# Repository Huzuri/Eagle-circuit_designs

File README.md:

# Eagle-circuit_designs
This are the circuit designed my Kaushik Huzuri using Camsoft Eagle software

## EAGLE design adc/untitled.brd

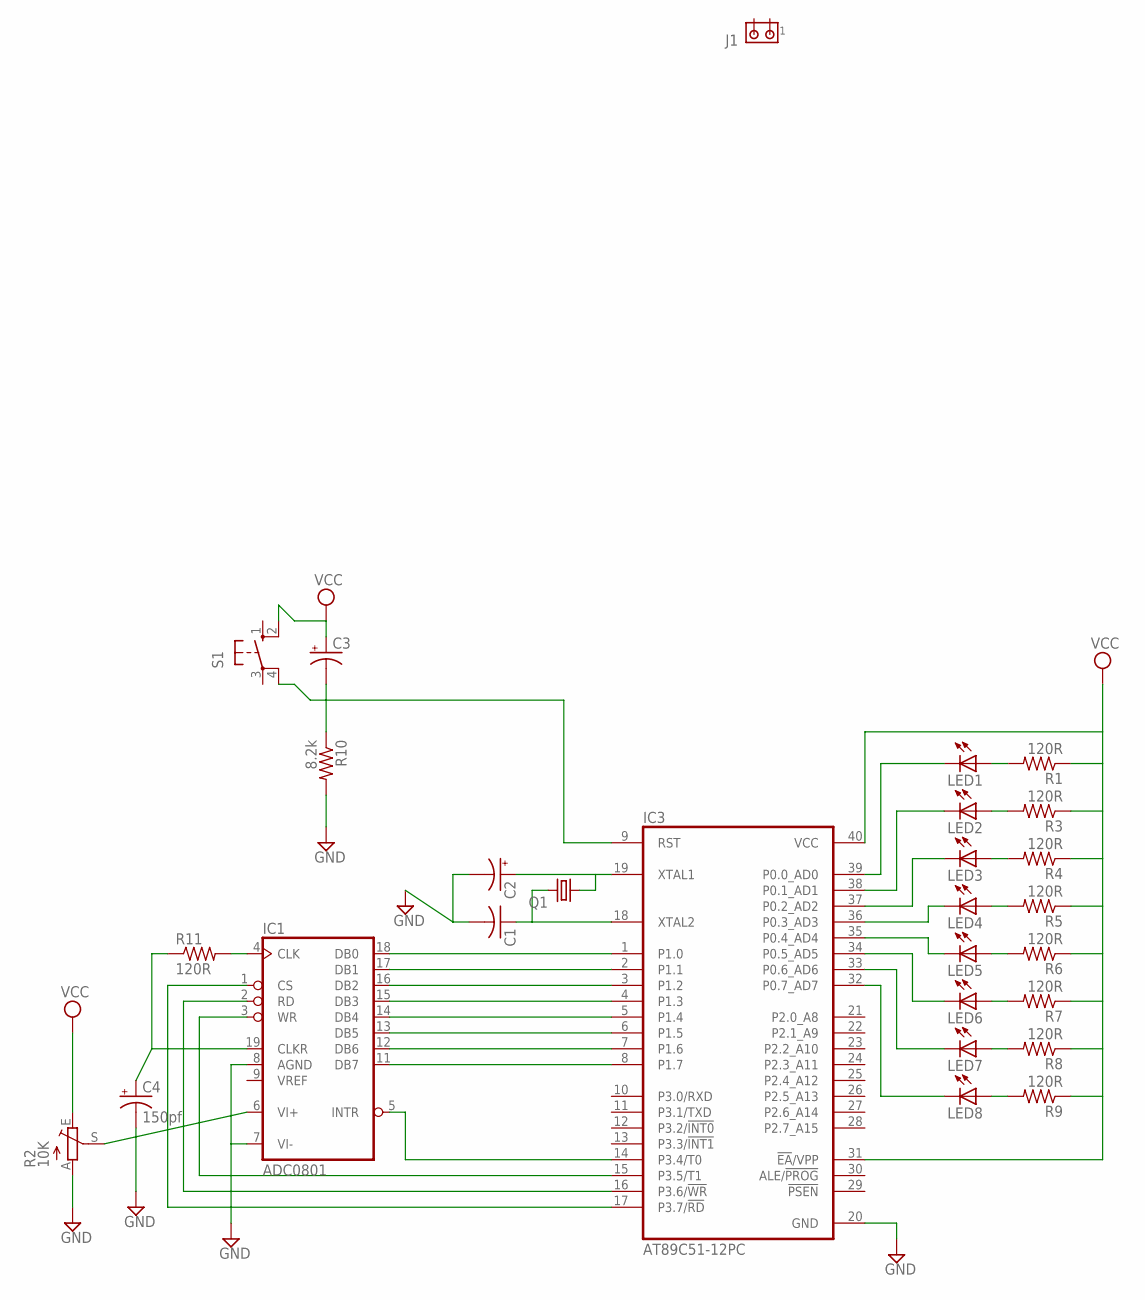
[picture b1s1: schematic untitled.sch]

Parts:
C1: C-US025-025X050; C025-025X050
C2, C3: CPOL-USE2.5-5V; E2,5-4R
C4: 150pf; E2,5-4R
IC1: ADC0801; DIL20
IC3: AT89C51-12PC; DIL40
J1: MTA02-100; 10X02MTA
LED1, LED2, LED3, LED4, LED5, LED6, LED7, LED8: LEDCHIP-LED0805; CHIP-LED0805
Q1: CRYSTALTC26H; TC26H
R1, R3, R4, R5, R6, R7, R8, R9, R11: 120R; R2512
R2: 10K; B25U
R10: 8.2k; R2512
S1: 10-XX; B3F-10XX

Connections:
GND: C1.2, C2.-, C4.-, IC1.7 (VI-), IC1.8 (AGND), IC1.10 (GND), IC3.20 (GND), R2.A, R10.2
unnamed: IC3.39 (P0.0_AD0), LED1.C
unnamed: IC3.32 (P0.7_AD7), LED8.C
unnamed: IC3.33 (P0.6_AD6), LED7.C
unnamed: IC3.38 (P0.1_AD1), LED2.C
unnamed: IC3.37 (P0.2_AD2), LED3.C
unnamed: IC3.34 (P0.5_AD5), LED6.C
unnamed: IC3.35 (P0.4_AD4), LED5.C
unnamed: IC3.36 (P0.3_AD3), LED4.C
unnamed: LED8.A, R9.2
unnamed: LED7.A, R8.2
unnamed: LED6.A, R7.2
unnamed: LED5.A, R6.2
unnamed: LED4.A, R5.2
unnamed: LED3.A, R4.2
unnamed: LED2.A, R3.2
unnamed: LED1.A, R1.2
unnamed: C2.+, IC3.19 (XTAL1), Q1.1
unnamed: C1.1, IC3.18 (XTAL2), Q1.2
unnamed: IC1.12 (DB6), IC3.7 (P1.6)
unnamed: C3.-, IC3.9 (RST), R10.1, S1.4 (P1)
unnamed: IC1.13 (DB5), IC3.6 (P1.5)
unnamed: IC1.14 (DB4), IC3.5 (P1.4)
unnamed: IC1.15 (DB3), IC3.4 (P1.3)
unnamed: IC1.16 (DB2), IC3.3 (P1.2)
unnamed: IC1.17 (DB1), IC3.2 (P1.1)
unnamed: IC1.11 (DB7), IC3.8 (P1.7)
unnamed: IC1.18 (DB0), IC3.1 (P1.0)
unnamed: IC1.5 (INTR), IC3.14 (P3.4/T0)
unnamed: IC1.3 (WR), IC3.15 (P3.5/T1)
unnamed: IC1.2 (RD), IC3.16 (P3.6/!WR)
unnamed: IC1.1 (CS), IC3.17 (P3.7/!RD)
unnamed: IC1.4 (CLK), R11.2
unnamed: C4.+, IC1.19 (CLKR), R11.1
unnamed: IC1.6 (VI+), R2.S
VCC: C3.+, IC1.20 (VCC), IC3.31 (!EA!/VPP), IC3.40 (VCC), R1.1, R2.E, R3.1, R4.1, R5.1, R6.1, R7.1, R8.1, R9.1, S1.2 (S1)

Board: 2 copper layers, 28 parts (0 on the bottom side), 36 nets, no tracks yet.

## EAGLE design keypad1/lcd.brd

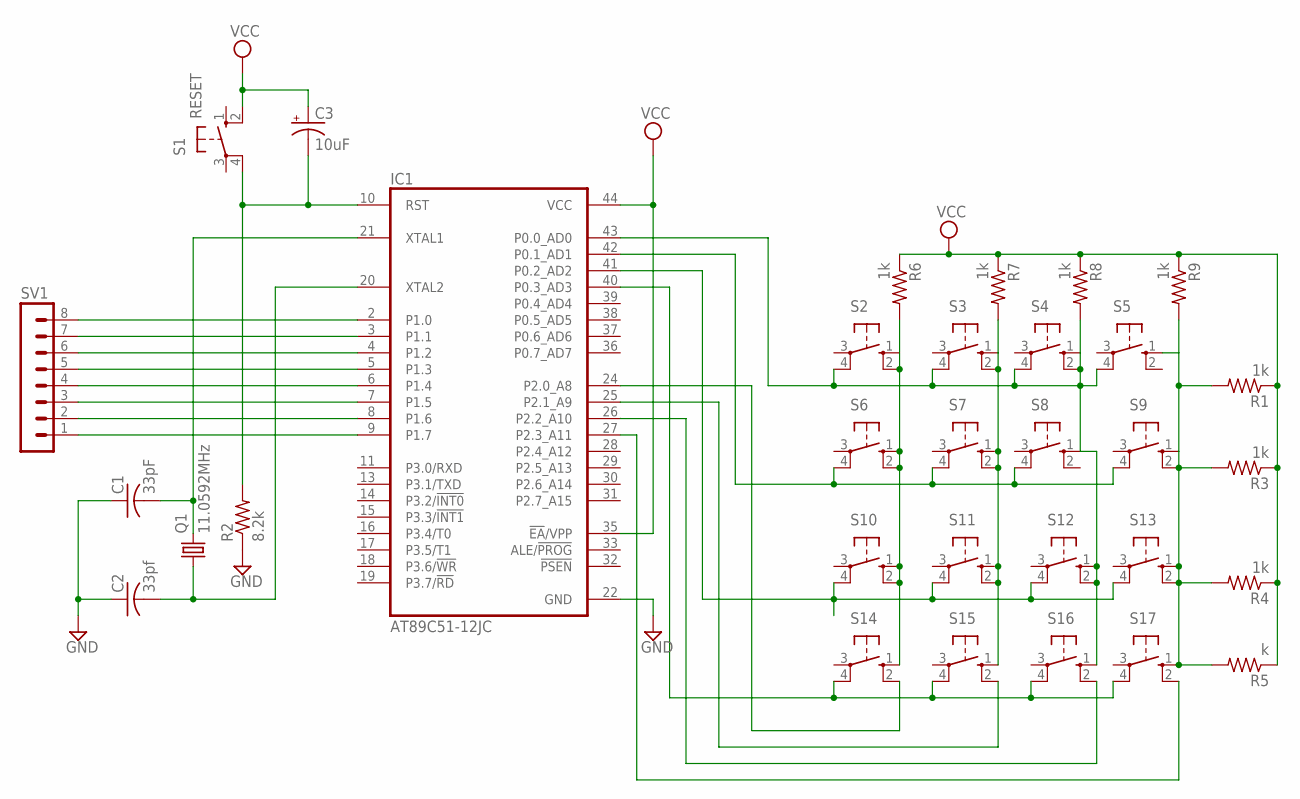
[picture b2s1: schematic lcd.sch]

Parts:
C1: 33pF; C025-025X050
C2: 33pf; C025-025X050
C3: 10uF; E2,5-5
IC1: AT89C51-12JC; PLCC44
Q1: 11.0592MHz; TC26H
R1, R3, R4, R6, R7, R8, R9: 1k; R2512
R2: 8.2k; R2512
R5: k; R2512
S1: RESET; B3F-10XX
S2, S3, S4, S5, S6, S7, S8, S9, S10, S11, S12, S13, S14, S15, S16, S17: 10-XX; B3F-10XX
SV1: MA08-1W

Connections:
GND: C1.1, C2.1, IC1.22 (GND), R2.1
unnamed: IC1.9 (P1.7), SV1.1
unnamed: IC1.8 (P1.6), SV1.2
unnamed: IC1.7 (P1.5), SV1.3
unnamed: IC1.6 (P1.4), SV1.4
unnamed: IC1.5 (P1.3), SV1.5
unnamed: IC1.4 (P1.2), SV1.6
unnamed: IC1.3 (P1.1), SV1.7
unnamed: IC1.2 (P1.0), SV1.8
unnamed: IC1.43 (P0.0_AD0), R8.2, S2.4 (P1), S3.4 (P1), S4.1 (S), S4.2 (S1), S4.4 (P1), S5.4 (P1), S8.1 (S), S12.1 (S), S12.2 (S1), S16.1 (S)
unnamed: IC1.42 (P0.1_AD1), S6.4 (P1), S7.4 (P1), S8.4 (P1), S9.4 (P1)
unnamed: IC1.41 (P0.2_AD2), S10.4 (P1), S11.4 (P1), S12.4 (P1), S13.4 (P1)
unnamed: C1.2, IC1.21 (XTAL1), Q1.2
unnamed: C2.2, IC1.20 (XTAL2), Q1.1
unnamed: IC1.40 (P0.3_AD3), S14.4 (P1), S15.4 (P1), S16.4 (P1), S17.4 (P1)
unnamed: IC1.25 (P2.1_A9), S15.2 (S1)
unnamed: C3.-, IC1.10 (RST), R2.2, S1.4 (P1)
unnamed: IC1.24 (P2.0_A8), S14.2 (S1)
unnamed: R6.2, S2.1 (S), S2.2 (S1), S6.1 (S), S6.2 (S1), S10.1 (S), S10.2 (S1), S14.1 (S)
unnamed: R7.2, S3.1 (S), S3.2 (S1), S7.1 (S), S7.2 (S1), S11.1 (S), S11.2 (S1), S15.1 (S)
unnamed: R1.2, R3.2, R4.2, R5.2, R9.2, S5.1 (S), S9.1 (S), S9.2 (S1), S13.1 (S), S13.2 (S1), S17.1 (S)
unnamed: IC1.26 (P2.2_A10), S16.2 (S1)
unnamed: IC1.27 (P2.3_A11), S17.2 (S1)
VCC: C3.+, IC1.35 (!EA!/VPP), IC1.44 (VCC), R1.1, R3.1, R4.1, R5.1, R6.1, R7.1, R8.1, R9.1, S1.2 (S1)

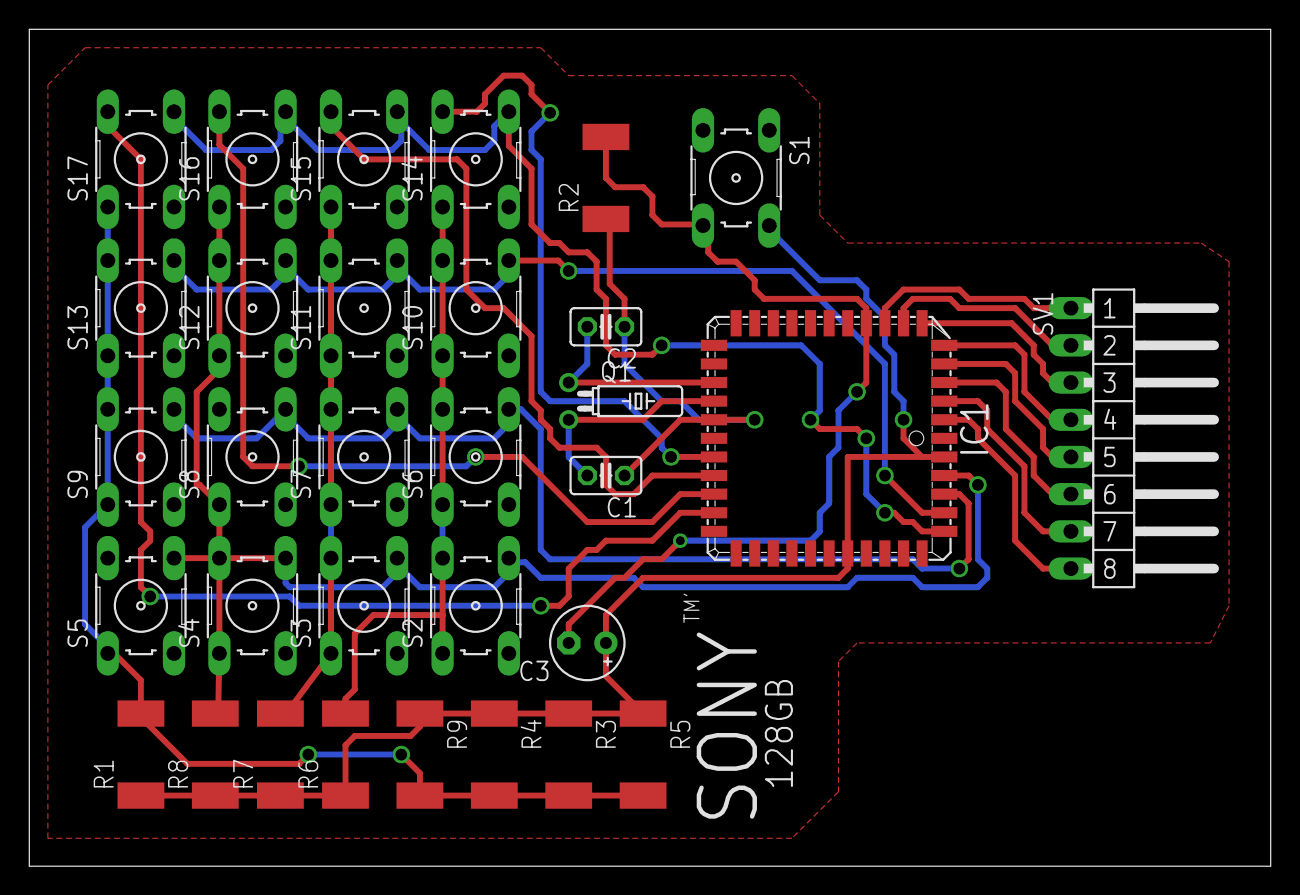
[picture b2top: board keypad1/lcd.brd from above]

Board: 2 copper layers, 84.8 x 57.1 mm, 32 parts (0 on the bottom side), 24 nets.

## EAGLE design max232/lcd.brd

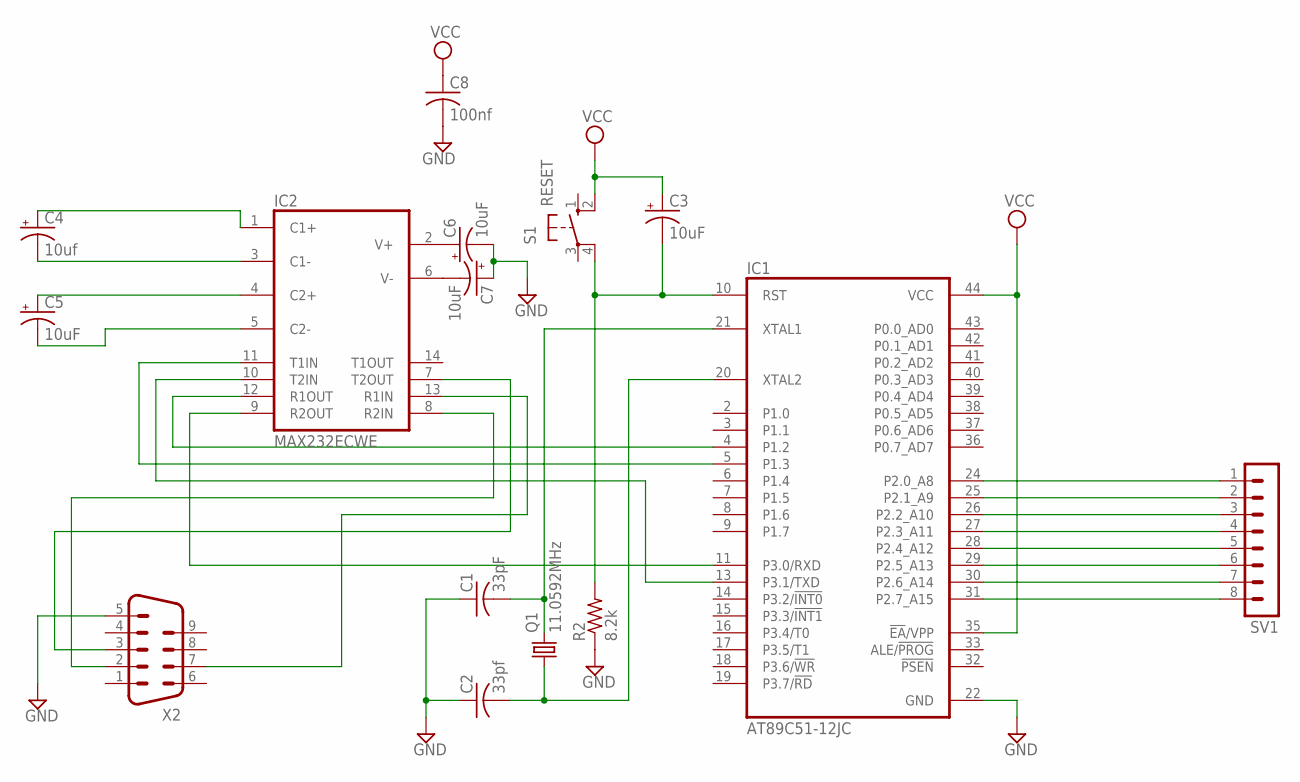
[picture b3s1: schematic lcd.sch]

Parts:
C1: 33pF; C025-025X050
C2: 33pf; C025-025X050
C3, C5, C6, C7: 10uF; E2,5-5
C4: 10uf; E2,5-5
C8: 100nf; C025-025X050
IC1: AT89C51-12JC; PLCC44
IC2: MAX232ECWE; SO16L
Q1: 11.0592MHz; TC26H
R2: 8.2k; R2512
S1: RESET; B3F-10XX
SV1: MA08-1W
X2: M09V

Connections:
GND: C1.1, C2.1, C6.-, C7.+, C8.2, IC1.22 (GND), IC2.15 (GND), R2.1, X2.5
unnamed: IC1.24 (P2.0_A8), SV1.1
unnamed: IC1.25 (P2.1_A9), SV1.2
unnamed: IC1.26 (P2.2_A10), SV1.3
unnamed: IC1.27 (P2.3_A11), SV1.4
unnamed: IC1.28 (P2.4_A12), SV1.5
unnamed: IC1.29 (P2.5_A13), SV1.6
unnamed: IC1.30 (P2.6_A14), SV1.7
unnamed: IC1.31 (P2.7_A15), SV1.8
unnamed: IC1.5 (P1.3), IC2.11 (T1IN)
unnamed: IC1.13 (P3.1/TXD), IC2.10 (T2IN)
unnamed: IC1.4 (P1.2), IC2.12 (R1OUT)
unnamed: C1.2, IC1.21 (XTAL1), Q1.2
unnamed: C2.2, IC1.20 (XTAL2), Q1.1
unnamed: IC1.11 (P3.0/RXD), IC2.9 (R2OUT)
unnamed: C4.+, IC2.1 (C1+)
unnamed: C4.-, IC2.3 (C1-)
unnamed: C3.-, IC1.10 (RST), R2.2, S1.4 (P1)
unnamed: C5.+, IC2.4 (C2+)
unnamed: C5.-, IC2.5 (C2-)
unnamed: C6.+, IC2.2 (V+)
unnamed: C7.-, IC2.6 (V-)
unnamed: IC2.7 (T2OUT), X2.3
unnamed: IC2.13 (R1IN), X2.7
unnamed: IC2.8 (R2IN), X2.2
VCC: C3.+, C8.1, IC1.35 (!EA!/VPP), IC1.44 (VCC), IC2.16 (VCC), S1.2 (S1)

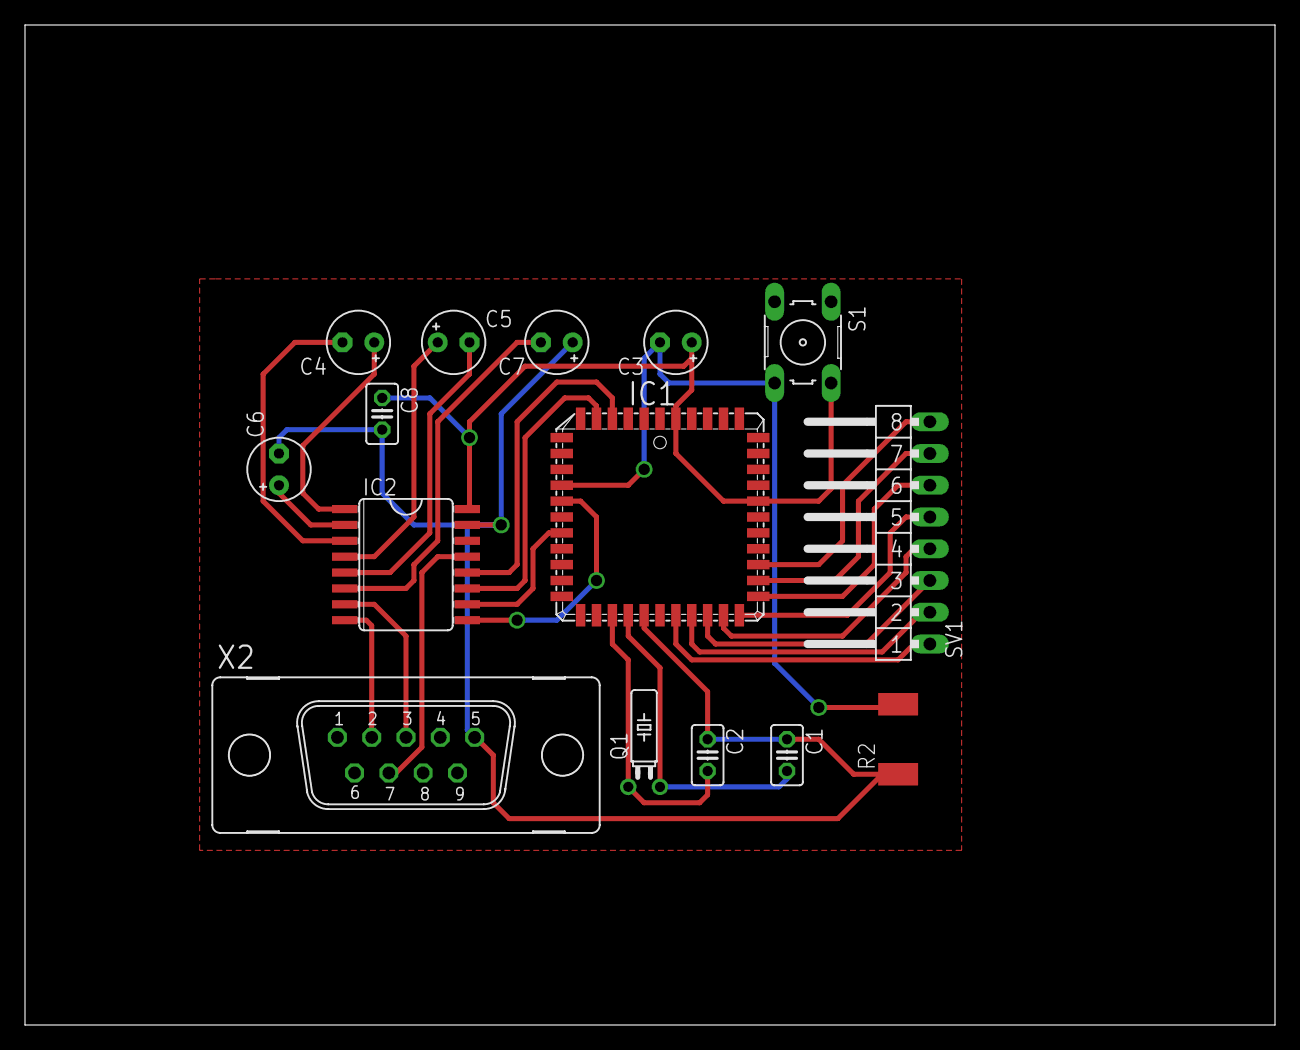
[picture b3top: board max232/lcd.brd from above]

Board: 2 copper layers, 100.0 x 80.0 mm, 15 parts (0 on the bottom side), 26 nets.

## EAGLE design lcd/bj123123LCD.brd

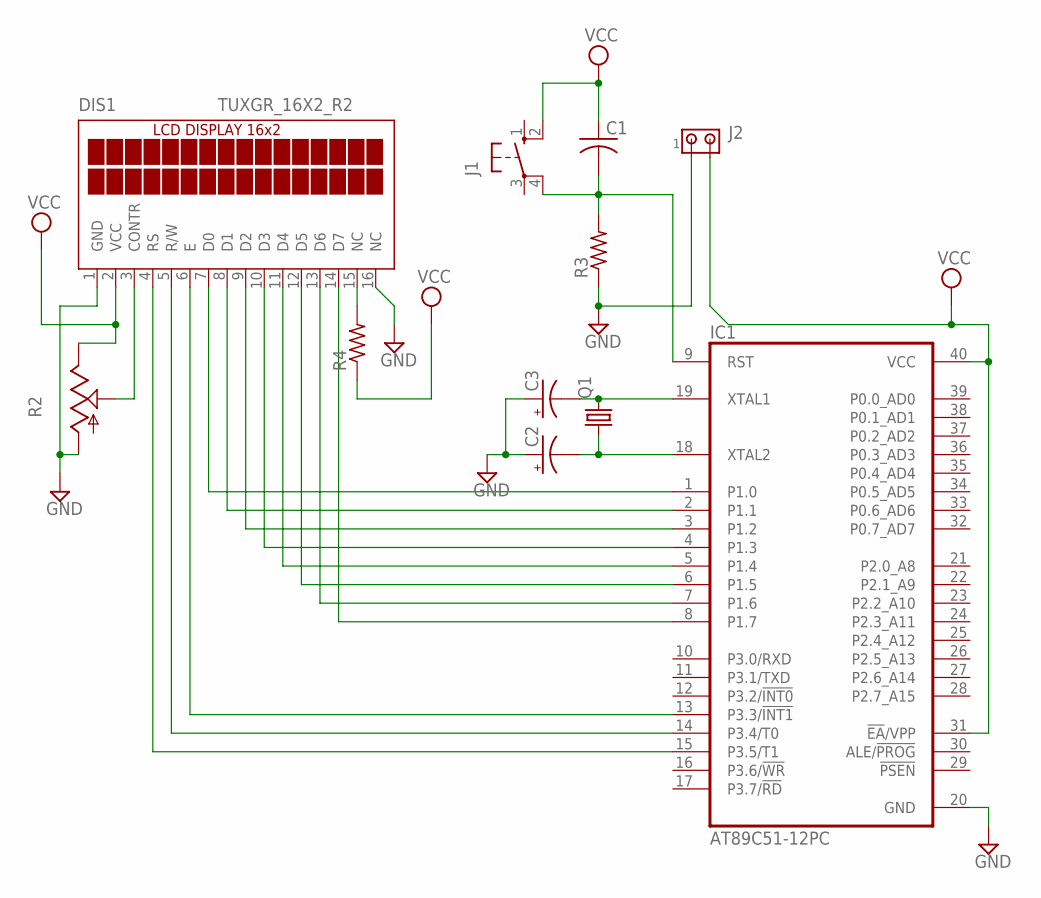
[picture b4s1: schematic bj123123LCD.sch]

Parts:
C1: C-US025-025X050; C025-025X050
C2, C3: CPOL-USE2.5-5; E2,5-5
DIS1: TUXGR_16X2_R2
IC1: AT89C51-12PC; DIL40
J1: 10-XX; B3F-10XX
J2: MTA02-100; 10X02MTA
Q1: CRYSTALTC26H; TC26H
R2: TRIM_US-B25U; B25U
R3, R4: R-US_R2512; R2512

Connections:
GND: C2.+, C3.+, DIS1.1 (GND), DIS1.16 (NC), IC1.20 (GND), J2.1, R2.A, R3.1
unnamed: DIS1.7 (D0), IC1.1 (P1.0)
unnamed: DIS1.8 (D1), IC1.2 (P1.1)
unnamed: DIS1.9 (D2), IC1.3 (P1.2)
unnamed: DIS1.10 (D3), IC1.4 (P1.3)
unnamed: DIS1.11 (D4), IC1.5 (P1.4)
unnamed: DIS1.12 (D5), IC1.6 (P1.5)
unnamed: DIS1.13 (D6), IC1.7 (P1.6)
unnamed: DIS1.14 (D7), IC1.8 (P1.7)
unnamed: DIS1.15 (NC), R4.2
unnamed: C3.-, IC1.19 (XTAL1), Q1.2
unnamed: C1.2, IC1.9 (RST), J1.4 (P1), R3.2
unnamed: C2.-, IC1.18 (XTAL2), Q1.1
unnamed: DIS1.6 (E), IC1.13 (P3.3/!INT1)
unnamed: DIS1.5 (R/W), IC1.14 (P3.4/T0)
unnamed: DIS1.3 (CONTR), R2.S
unnamed: DIS1.4 (RS), IC1.15 (P3.5/T1)
VCC: C1.1, DIS1.2 (VCC), IC1.31 (!EA!/VPP), IC1.40 (VCC), J1.2 (S1), J2.2, R2.E, R4.1

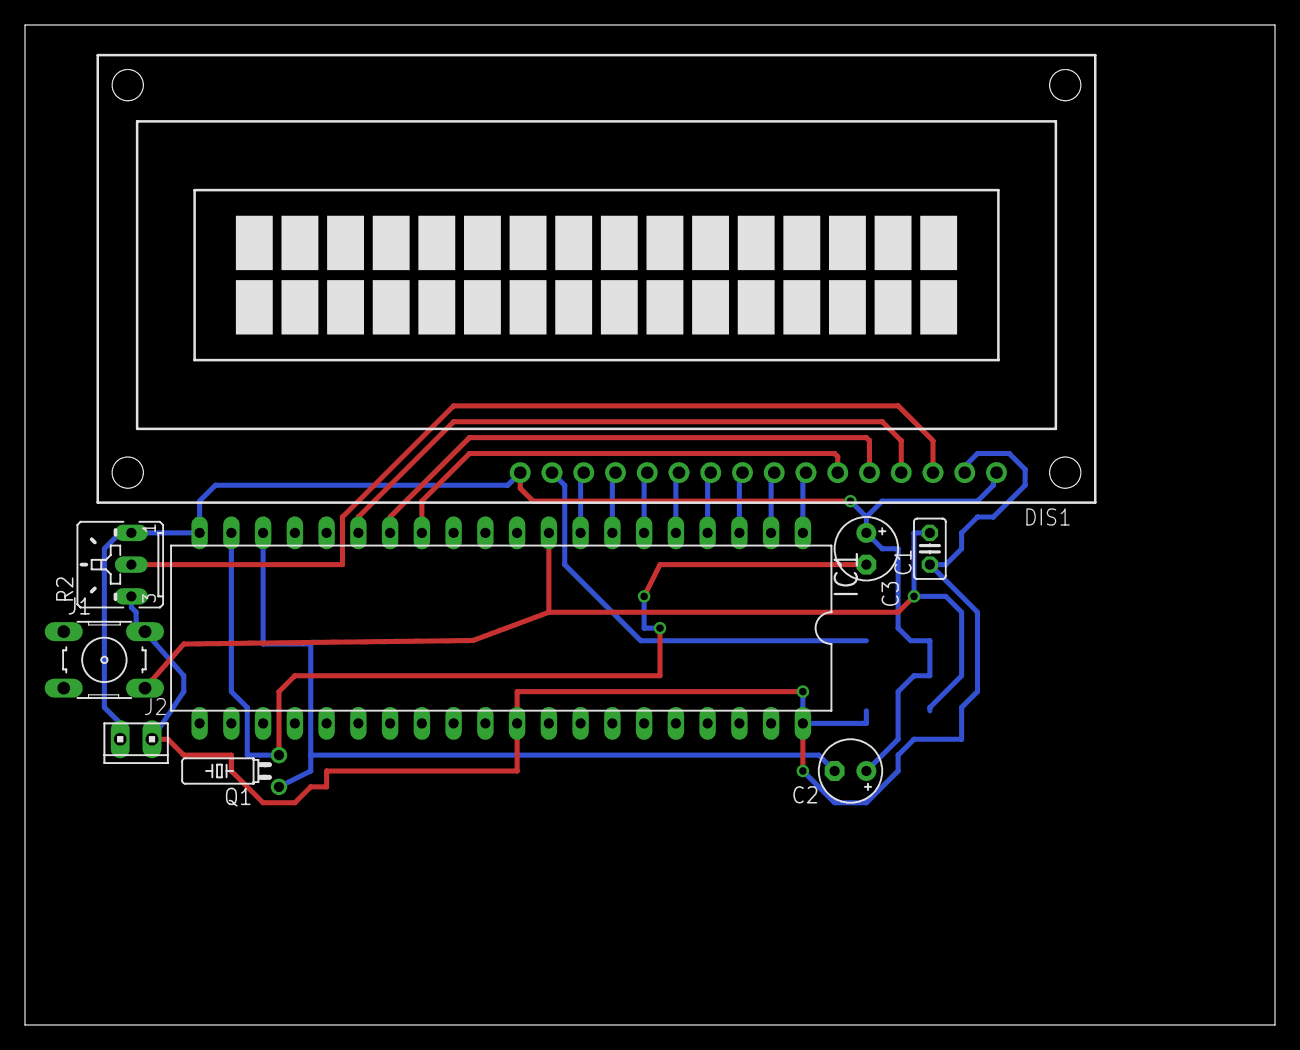
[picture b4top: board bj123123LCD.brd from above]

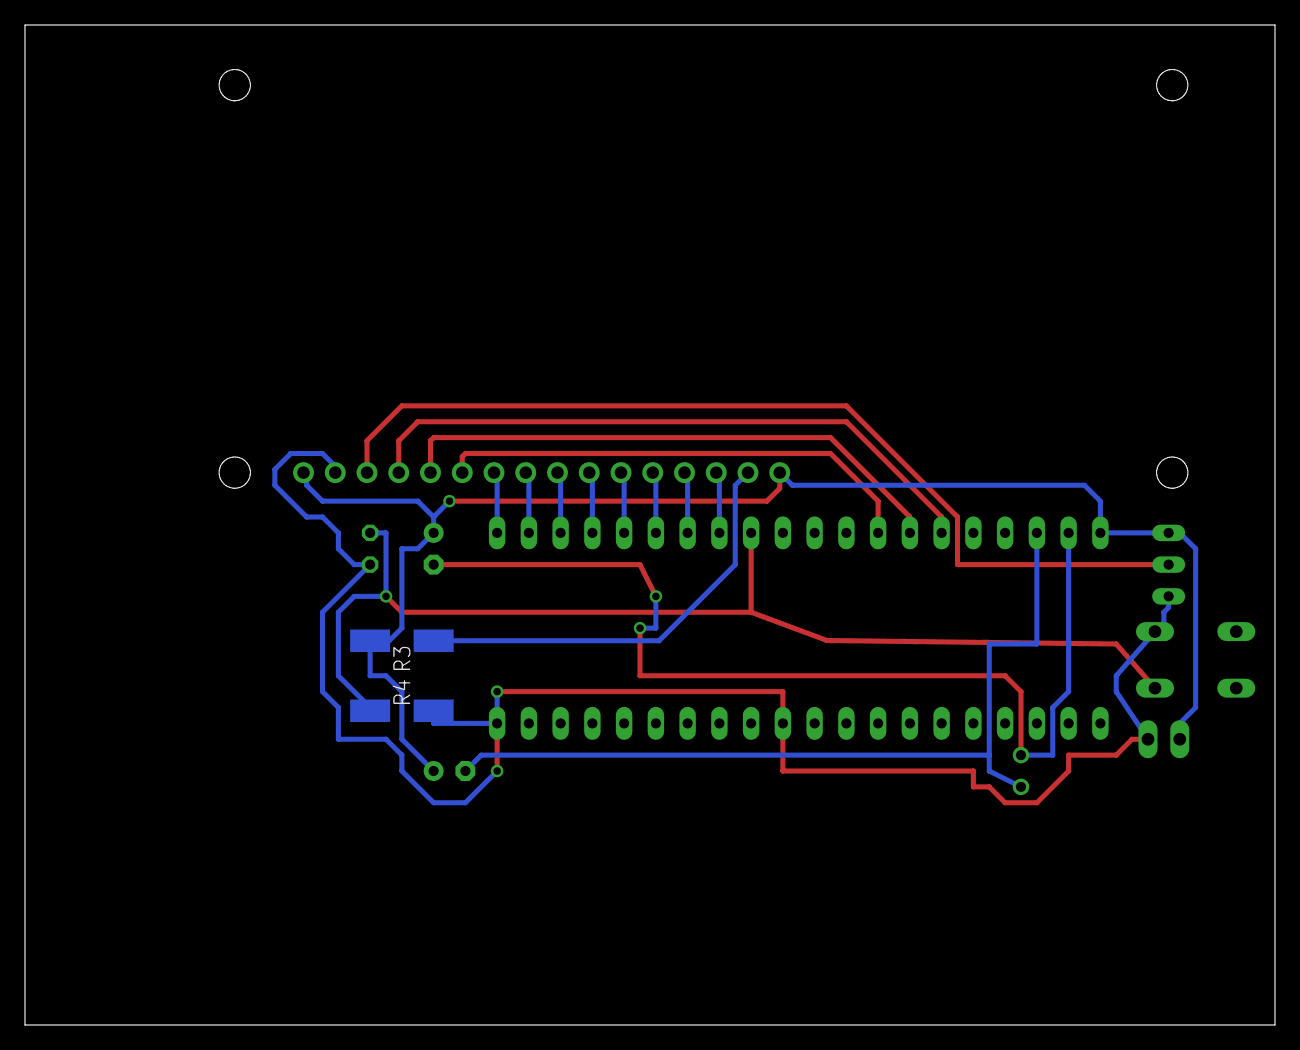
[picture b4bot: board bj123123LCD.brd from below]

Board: 2 copper layers, 100.0 x 80.0 mm, 11 parts (2 on the bottom side), 18 nets.

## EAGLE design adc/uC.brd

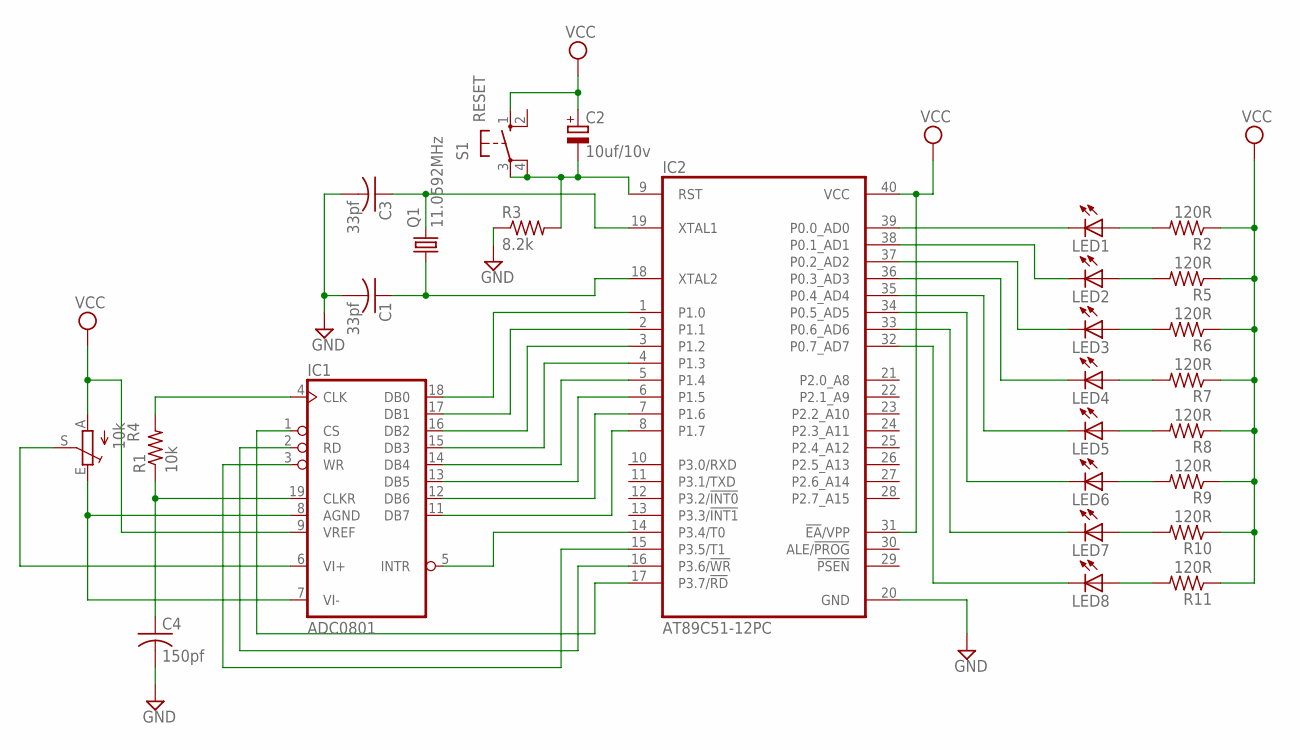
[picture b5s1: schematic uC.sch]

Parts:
C1, C3: 33pf; C025-025X050
C2: 10uf/10v; E2,5-5
C4: 150pf; C025-025X050
IC1: ADC0801; DIL20
IC2: AT89C51-12PC; DIL40
LED1, LED2, LED3, LED4, LED5, LED6, LED7, LED8: LEDCHIPLED_0805; CHIPLED_0805
Q1: 11.0592MHz; TC26H
R1: 10k; R2512
R2, R5, R6, R7, R8, R9, R10, R11: 120R; R2512
R3: 8.2k; R2512
R4: 10k; B25U
S1: RESET; B3F-10XX

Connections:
GND: C1.2, C3.2, C4.2, IC1.10 (GND), IC2.20 (GND), R3.1
unnamed: IC2.39 (P0.0_AD0), LED1.C
unnamed: IC2.38 (P0.1_AD1), LED2.C
unnamed: IC2.37 (P0.2_AD2), LED3.C
unnamed: IC2.36 (P0.3_AD3), LED4.C
unnamed: IC2.35 (P0.4_AD4), LED5.C
unnamed: IC2.34 (P0.5_AD5), LED6.C
unnamed: IC2.33 (P0.6_AD6), LED7.C
unnamed: IC2.32 (P0.7_AD7), LED8.C
unnamed: IC1.18 (DB0), IC2.1 (P1.0)
unnamed: IC1.17 (DB1), IC2.2 (P1.1)
unnamed: IC1.16 (DB2), IC2.3 (P1.2)
unnamed: IC1.15 (DB3), IC2.4 (P1.3)
unnamed: IC1.14 (DB4), IC2.5 (P1.4)
unnamed: IC1.13 (DB5), IC2.6 (P1.5)
unnamed: IC1.12 (DB6), IC2.7 (P1.6)
unnamed: IC1.11 (DB7), IC2.8 (P1.7)
unnamed: IC1.1 (CS), IC2.17 (P3.7/!RD)
unnamed: IC1.2 (RD), IC2.16 (P3.6/!WR)
unnamed: IC1.3 (WR), IC2.15 (P3.5/T1)
unnamed: IC1.5 (INTR), IC2.14 (P3.4/T0)
unnamed: IC1.6 (VI+), R4.S
unnamed: IC1.4 (CLK), R1.2
unnamed: IC1.7 (VI-), IC1.8 (AGND), R4.E
unnamed: C4.1, IC1.19 (CLKR), R1.1
unnamed: C2.-, IC2.9 (RST), R3.2, S1.3, S1.4 (P1)
unnamed: LED1.A, R2.2
unnamed: LED2.A, R5.2
unnamed: C3.1, IC2.19 (XTAL1), Q1.2
unnamed: C1.1, IC2.18 (XTAL2), Q1.1
unnamed: LED3.A, R6.2
unnamed: LED4.A, R7.2
unnamed: LED5.A, R8.2
unnamed: LED6.A, R9.2
unnamed: LED7.A, R10.2
unnamed: LED8.A, R11.2
VCC: C2.+, IC1.9 (VREF), IC1.20 (VCC), IC2.31 (!EA!/VPP), IC2.40 (VCC), R2.1, R4.A, R5.1, R6.1, R7.1, R8.1, R9.1, R10.1, R11.1, S1.1 (S)

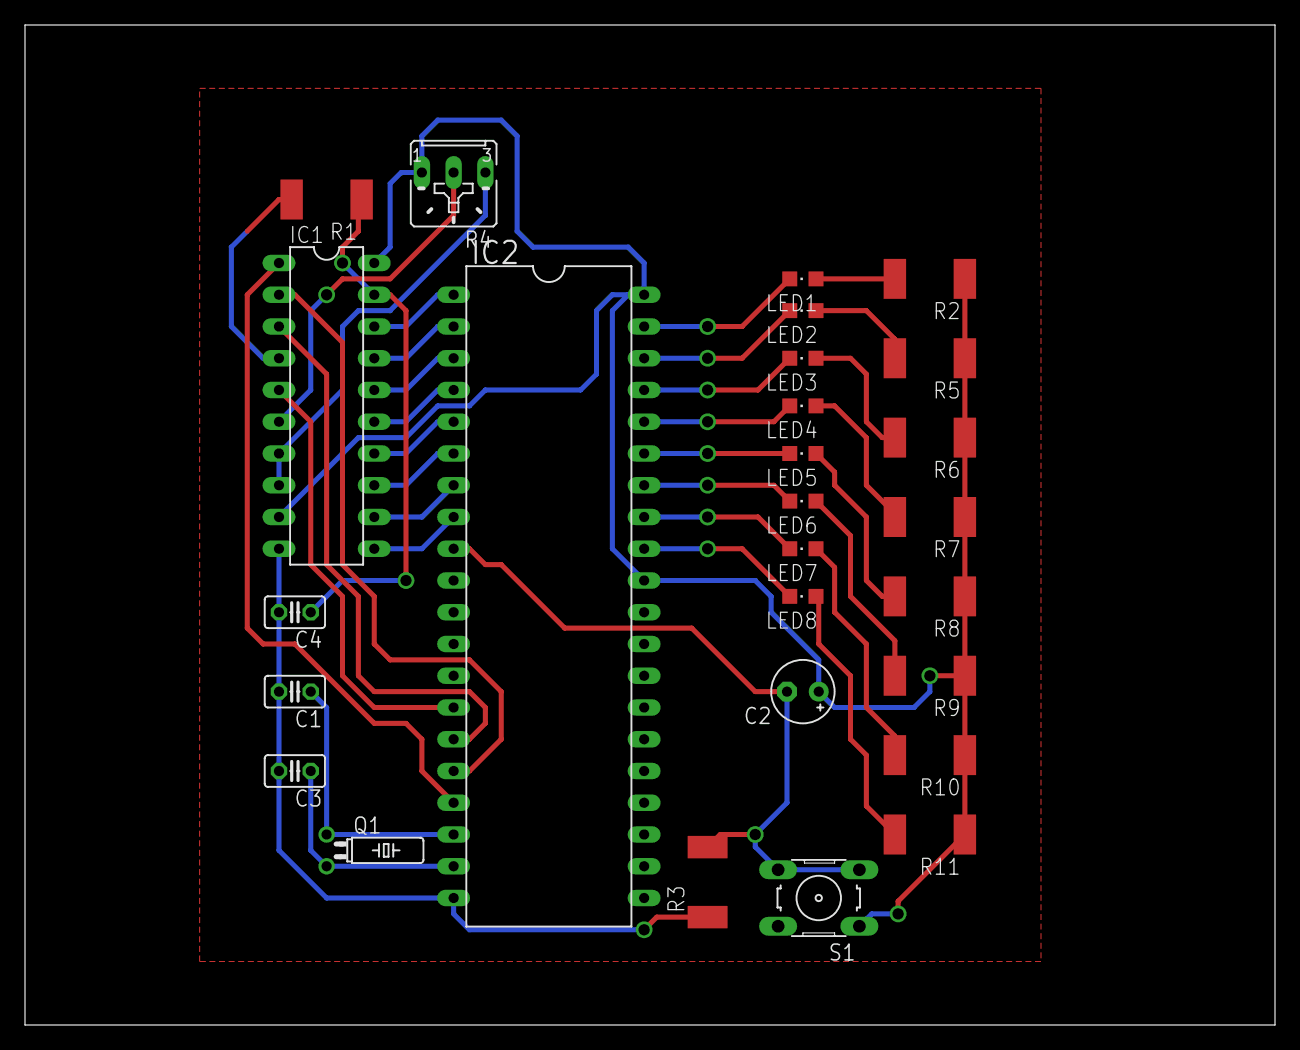
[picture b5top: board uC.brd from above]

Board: 2 copper layers, 100.0 x 80.0 mm, 27 parts (0 on the bottom side), 37 nets.

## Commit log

2019-04-13 7 segment file upload
2019-04-13 my files
